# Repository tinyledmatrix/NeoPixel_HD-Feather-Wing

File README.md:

## NeoPixel_HD FeatherWing PCB

More Information and Images also here: https://hackaday.io/project/168448

Inspired and based on Adafruit's NeoPixel FeatherWing, but with more Pixels! This readme is also partly transfered from Adafruit. 

You can find the original here:
http://www.adafruit.com/products/2945  or 
https://github.com/adafruit/Adafruit-NeoPixel-FeatherWing-PCB

This is the NeoPixel FeatherWing, a 9x22 RGB LED Add-on For All Feather Boards! Using Feather Stacking Headers or Feather Female Headers you can connect a FeatherWing on top or bottom of your Feather board and make your Feather board strut like a peacock at a rave.

Put on your sunglasses before staring into these 198 configurable eye-blistering RGB LEDs. Arranged in a 9x22 matrix, each pixel is individually addressable. Only one pin is required to control all the LEDs. On the bottom we have jumpers for the DIN line to any of the I/O pins on a Feather.  Works with any/all of our Feathers! You can cut the default jumper trace and use any pin you like. (In particular, the default pin for Feather Huzzah ESP8266 must be moved, try pin #15!) It works with but is not recommended for ESP32 Feather at this time due to a NeoPixel timing issue that makes it hard to control more than 30 pixels

PCB files for NeoPixel_HD FeatherWing. The format is EagleCAD schematic and board layout

### License

Creative Commons Attribution/Share-Alike, all text above must be included in any redistribution. 
See license.txt for additional information.

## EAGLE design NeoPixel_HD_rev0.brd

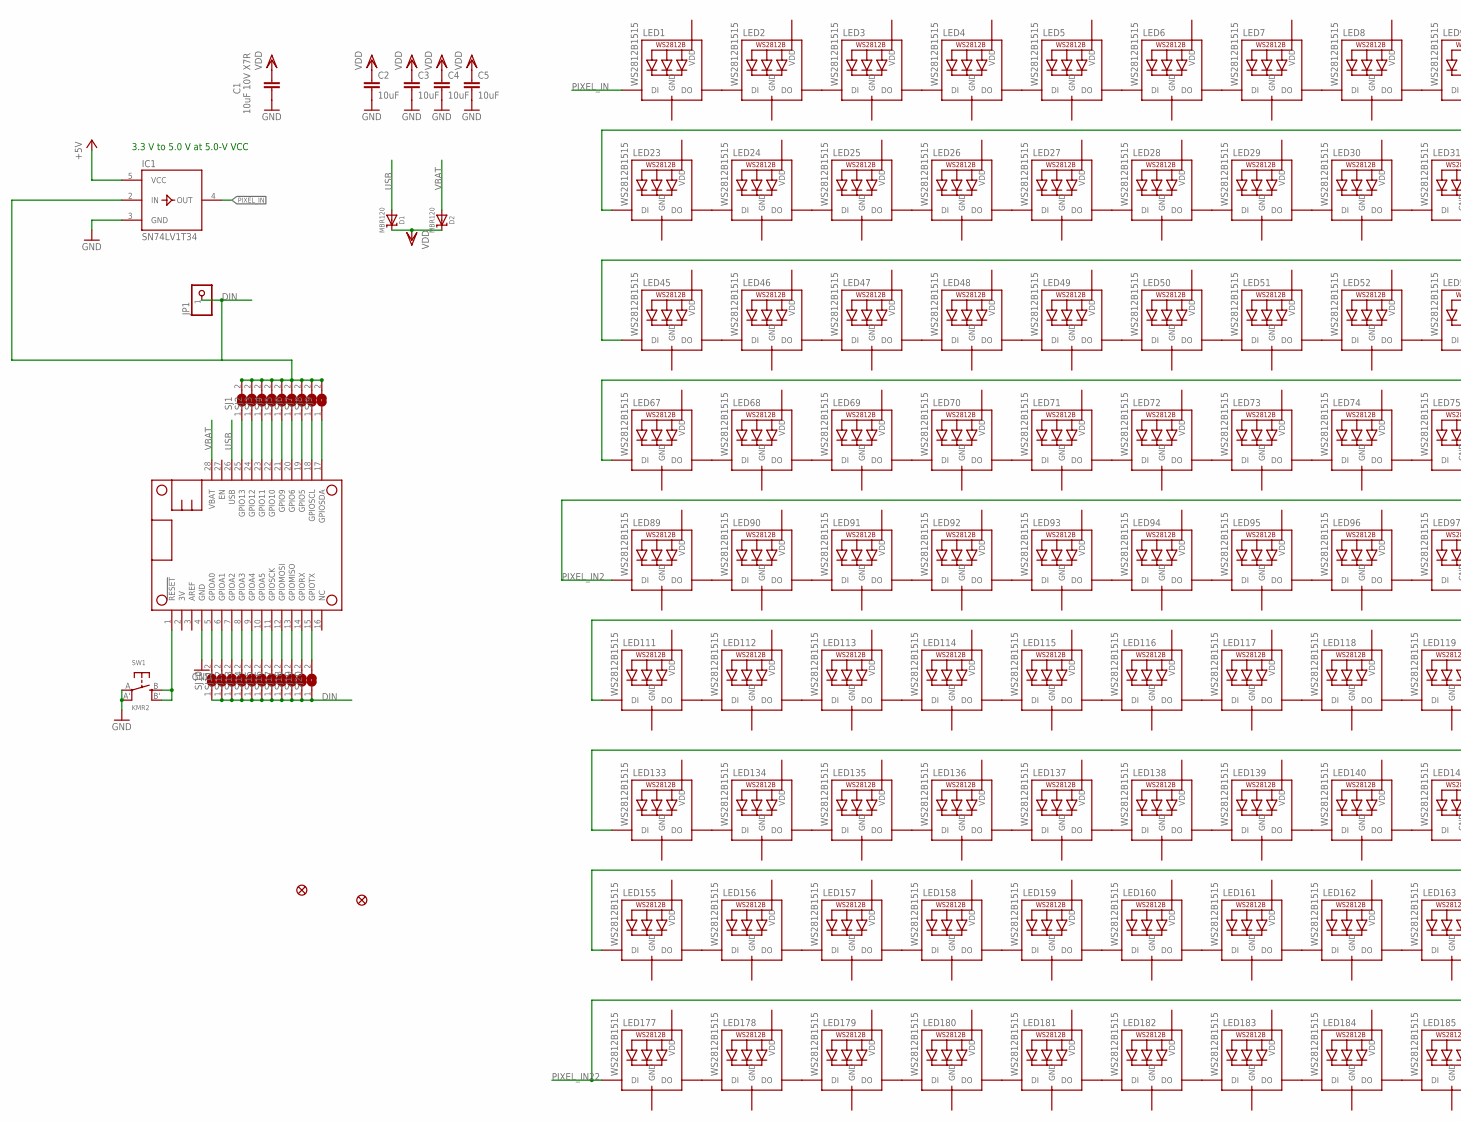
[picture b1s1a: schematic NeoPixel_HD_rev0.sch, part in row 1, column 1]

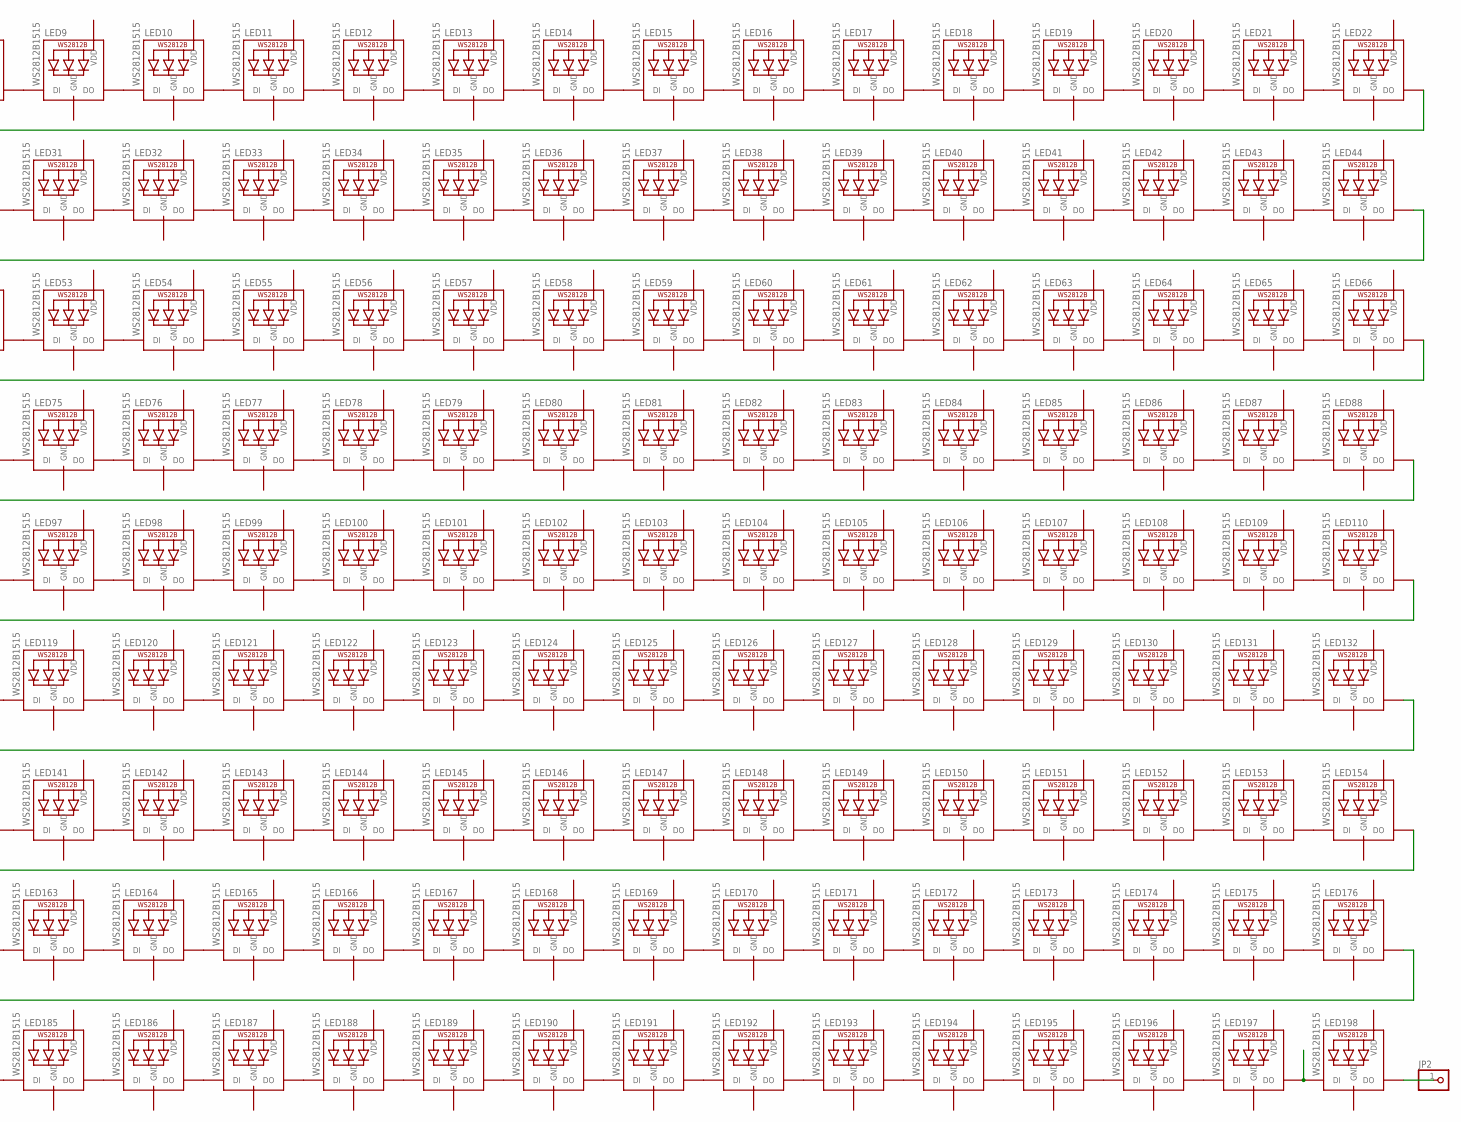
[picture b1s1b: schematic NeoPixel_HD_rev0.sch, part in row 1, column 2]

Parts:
C1: 10uF 10V X7R; C0603-VISHAY
C2, C3, C4, C5: 10uF; C0603-VISHAY
D1, D2: MBR120; SOD-123
FID1, FID2: FIDUCIAL""; FIDUCIAL_1MM
IC1: SN74LV1T34; DCK_R-PDSO-G5
JP1, JP2: HEADER-1X1ROUND; 1X01_ROUND
LED1, LED2, LED3, LED4, LED5, LED6, LED7, LED8, LED9, LED10, LED11, LED12, LED13, LED14, LED15, LED16, LED17, LED18, LED19, LED20, LED21, LED22, LED23, LED24, LED25, LED26, LED27, LED28, LED29, LED30, LED31, LED32, LED33, LED34, LED35, LED36, LED37, LED38, LED39, LED40, LED41, LED42, LED43, LED44, LED45, LED46, LED47, LED48, LED49, LED50, LED51, LED52, LED53, LED54, LED55, LED56, LED57, LED58, LED59, LED60, LED61, LED62, LED63, LED64, LED65, LED66, LED67, LED68, LED69, LED70, LED71, LED72, LED73, LED74, LED75, LED76, LED77, LED78, LED79, LED80, LED81, LED82, LED83, LED84, LED85, LED86, LED87, LED88, LED89, LED90, LED91, LED92, LED93, LED94, LED95, LED96, LED97, LED98, LED99, LED100, LED101, LED102, LED103, LED104, LED105, LED106, LED107, LED108, LED109, LED110, LED111, LED112, LED113, LED114, LED115, LED116, LED117, LED118, LED119, LED120, LED121, LED122, LED123, LED124, LED125, LED126, LED127, LED128, LED129, LED130, LED131, LED132, LED133, LED134, LED135, LED136, LED137, LED138, LED139, LED140, LED141, LED142, LED143, LED144, LED145, LED146, LED147, LED148, LED149, LED150, LED151, LED152, LED153, LED154, LED155, LED156, LED157, LED158, LED159, LED160, LED161, LED162, LED163, LED164, LED165, LED166, LED167, LED168, LED169, LED170, LED171, LED172, LED173, LED174, LED175, LED176, LED177, LED178, LED179, LED180, LED181, LED182, LED183, LED184, LED185, LED186, LED187, LED188, LED189, LED190, LED191, LED192, LED193, LED194, LED195, LED196, LED197, LED198: WS2812B1515; LED1515
MS1: FEATHERWING
SJ1, SJ2, SJ3, SJ4, SJ5, SJ7, SJ8, SJ9, SJ10, SJ11, SJ12, SJ13, SJ14, SJ15, SJ16, SJ17, SJ18, SJ19, SJ20: SOLDERJUMPER; SOLDERJUMPER_ARROW_NOPASTE
SJ6: SOLDERJUMPERCLOSED; SOLDERJUMPER_CLOSEDWIRE
SW1: KMR2; BTN_KMR2_4.6X2.8

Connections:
D6: MS1.20 (GPIO6), SJ6.1
DIN: IC1.2 (IN), JP1.1, SJ1.2, SJ2.2, SJ3.2, SJ4.2, SJ5.2, SJ6.2, SJ7.2, SJ8.2, SJ9.2, SJ10.1, SJ11.1, SJ12.1, SJ13.1, SJ14.1, SJ15.1, SJ16.1, SJ17.1, SJ18.1, SJ19.1, SJ20.1
GND: C1.2, C2.2, C3.2, C4.2, C5.2, IC1.3 (GND), LED1.GND, LED2.GND, LED3.GND, LED4.GND, LED5.GND, LED6.GND, LED7.GND, LED8.GND, LED9.GND, LED10.GND, LED11.GND, LED12.GND, LED13.GND, LED14.GND, LED15.GND, LED16.GND, LED17.GND, LED18.GND, LED19.GND, LED20.GND, LED21.GND, LED22.GND, LED23.GND, LED24.GND, LED25.GND, LED26.GND, LED27.GND, LED28.GND, LED29.GND, LED30.GND, LED31.GND, LED32.GND, LED33.GND, LED34.GND, LED35.GND, LED36.GND, LED37.GND, LED38.GND, LED39.GND, LED40.GND, LED41.GND, LED42.GND, LED43.GND, LED44.GND, LED45.GND, LED46.GND, LED47.GND, LED48.GND, LED49.GND, LED50.GND, LED51.GND, LED52.GND, LED53.GND, LED54.GND, LED55.GND, LED56.GND, LED57.GND, LED58.GND, LED59.GND, LED60.GND, LED61.GND, LED62.GND, LED63.GND, LED64.GND, LED65.GND, LED66.GND, LED67.GND, LED68.GND, LED69.GND, LED70.GND, LED71.GND, LED72.GND, LED73.GND, LED74.GND, LED75.GND, LED76.GND, LED77.GND, LED78.GND, LED79.GND, LED80.GND, LED81.GND, LED82.GND, LED83.GND, LED84.GND, LED85.GND, LED86.GND, LED87.GND, LED88.GND, LED89.GND, LED90.GND, LED91.GND, LED92.GND, LED93.GND, LED94.GND, LED95.GND, LED96.GND, LED97.GND, LED98.GND, LED99.GND, LED100.GND, LED101.GND, LED102.GND, LED103.GND, LED104.GND, LED105.GND, LED106.GND, LED107.GND, LED108.GND, LED109.GND, LED110.GND, LED111.GND, LED112.GND, LED113.GND, LED114.GND, LED115.GND, LED116.GND, LED117.GND, LED118.GND, LED119.GND, LED120.GND, LED121.GND, LED122.GND, LED123.GND, LED124.GND, LED125.GND, LED126.GND, LED127.GND, LED128.GND, LED129.GND, LED130.GND, LED131.GND, LED132.GND, LED133.GND, LED134.GND, LED135.GND, LED136.GND, LED137.GND, LED138.GND, LED139.GND, LED140.GND, LED141.GND, LED142.GND, LED143.GND, LED144.GND, LED145.GND, LED146.GND, LED147.GND, LED148.GND, LED149.GND, LED150.GND, LED151.GND, LED152.GND, LED153.GND, LED154.GND, LED155.GND, LED156.GND, LED157.GND, LED158.GND, LED159.GND, LED160.GND, LED161.GND, LED162.GND, LED163.GND, LED164.GND, LED165.GND, LED166.GND, LED167.GND, LED168.GND, LED169.GND, LED170.GND, LED171.GND, LED172.GND, LED173.GND, LED174.GND, LED175.GND, LED176.GND, LED177.GND, LED178.GND, LED179.GND, LED180.GND, LED181.GND, LED182.GND, LED183.GND, LED184.GND, LED185.GND, LED186.GND, LED187.GND, LED188.GND, LED189.GND, LED190.GND, LED191.GND, LED192.GND, LED193.GND, LED194.GND, LED195.GND, LED196.GND, LED197.GND, LED198.GND, MS1.4 (GND), SW1.A, SW1.A' (P1)
unnamed: LED42.DOUT (DO), LED43.DIN (DI)
unnamed: LED43.DOUT (DO), LED44.DIN (DI)
unnamed: MS1.25 (GPIO13), SJ1.1
unnamed: MS1.15 (GPIOTX), SJ20.2
unnamed: MS1.24 (GPIO12), SJ2.1
unnamed: MS1.14 (GPIORX), SJ19.2
unnamed: MS1.13 (GPIOMISO), SJ18.2
unnamed: MS1.12 (GPIOMOSI), SJ17.2
unnamed: MS1.11 (GPIOSCK), SJ16.2
unnamed: MS1.10 (GPIOA5), SJ15.2
unnamed: MS1.9 (GPIOA4), SJ14.2
unnamed: MS1.8 (GPIOA3), SJ13.2
unnamed: MS1.7 (GPIOA2), SJ12.2
unnamed: MS1.6 (GPIOA1), SJ11.2
unnamed: MS1.5 (GPIOA0), SJ10.2
unnamed: LED14.DOUT (DO), LED15.DIN (DI)
unnamed: LED45.DOUT (DO), LED46.DIN (DI)
unnamed: MS1.1 (!RESET), SW1.B (S), SW1.B' (S1)
unnamed: MS1.23 (GPIO11), SJ3.1
unnamed: MS1.22 (GPIO10), SJ4.1
unnamed: MS1.21 (GPIO9), SJ5.1
unnamed: JP2.1, LED198.DOUT (DO)
unnamed: MS1.19 (GPIO5), SJ7.1
unnamed: MS1.18 (GPIOSCL), SJ8.1
unnamed: MS1.17 (GPIOSDA), SJ9.1
unnamed: LED46.DOUT (DO), LED47.DIN (DI)
unnamed: LED47.DOUT (DO), LED48.DIN (DI)
unnamed: LED48.DOUT (DO), LED49.DIN (DI)
unnamed: LED49.DOUT (DO), LED50.DIN (DI)
unnamed: LED50.DOUT (DO), LED51.DIN (DI)
unnamed: LED51.DOUT (DO), LED52.DIN (DI)
unnamed: LED52.DOUT (DO), LED53.DIN (DI)
unnamed: LED54.DOUT (DO), LED55.DIN (DI)
unnamed: LED53.DOUT (DO), LED54.DIN (DI)
unnamed: LED55.DOUT (DO), LED56.DIN (DI)
unnamed: LED56.DOUT (DO), LED57.DIN (DI)
unnamed: LED59.DOUT (DO), LED60.DIN (DI)
unnamed: LED60.DOUT (DO), LED61.DIN (DI)
unnamed: LED61.DOUT (DO), LED62.DIN (DI)
unnamed: LED62.DOUT (DO), LED63.DIN (DI)
unnamed: LED63.DOUT (DO), LED64.DIN (DI)
unnamed: LED64.DOUT (DO), LED65.DIN (DI)
unnamed: LED65.DOUT (DO), LED66.DIN (DI)
unnamed: LED66.DOUT (DO), LED67.DIN (DI)
unnamed: LED68.DOUT (DO), LED69.DIN (DI)
unnamed: LED67.DOUT (DO), LED68.DIN (DI)
unnamed: LED69.DOUT (DO), LED70.DIN (DI)
unnamed: LED70.DOUT (DO), LED71.DIN (DI)
unnamed: LED73.DOUT (DO), LED74.DIN (DI)
unnamed: LED74.DOUT (DO), LED75.DIN (DI)
unnamed: LED75.DOUT (DO), LED76.DIN (DI)
unnamed: LED76.DOUT (DO), LED77.DIN (DI)
unnamed: LED77.DOUT (DO), LED78.DIN (DI)
unnamed: LED1.DOUT (DO), LED2.DIN (DI)
unnamed: LED2.DOUT (DO), LED3.DIN (DI)
unnamed: LED3.DOUT (DO), LED4.DIN (DI)
unnamed: LED4.DOUT (DO), LED5.DIN (DI)
unnamed: LED5.DOUT (DO), LED6.DIN (DI)
unnamed: LED6.DOUT (DO), LED7.DIN (DI)
unnamed: LED7.DOUT (DO), LED8.DIN (DI)
unnamed: LED8.DOUT (DO), LED9.DIN (DI)
unnamed: LED10.DOUT (DO), LED11.DIN (DI)
unnamed: LED9.DOUT (DO), LED10.DIN (DI)
unnamed: LED11.DOUT (DO), LED12.DIN (DI)
unnamed: LED12.DOUT (DO), LED13.DIN (DI)
unnamed: LED15.DOUT (DO), LED16.DIN (DI)
unnamed: LED16.DOUT (DO), LED17.DIN (DI)
unnamed: LED17.DOUT (DO), LED18.DIN (DI)
unnamed: LED18.DOUT (DO), LED19.DIN (DI)
unnamed: LED19.DOUT (DO), LED20.DIN (DI)
unnamed: LED20.DOUT (DO), LED21.DIN (DI)
unnamed: LED21.DOUT (DO), LED22.DIN (DI)
unnamed: LED22.DOUT (DO), LED23.DIN (DI)
unnamed: LED24.DOUT (DO), LED25.DIN (DI)
unnamed: LED23.DOUT (DO), LED24.DIN (DI)
unnamed: LED25.DOUT (DO), LED26.DIN (DI)
unnamed: LED26.DOUT (DO), LED27.DIN (DI)
unnamed: LED29.DOUT (DO), LED30.DIN (DI)
unnamed: LED30.DOUT (DO), LED31.DIN (DI)
unnamed: LED31.DOUT (DO), LED32.DIN (DI)
unnamed: LED32.DOUT (DO), LED33.DIN (DI)
unnamed: LED33.DOUT (DO), LED34.DIN (DI)
unnamed: LED34.DOUT (DO), LED35.DIN (DI)
unnamed: LED35.DOUT (DO), LED36.DIN (DI)
unnamed: LED36.DOUT (DO), LED37.DIN (DI)
unnamed: LED38.DOUT (DO), LED39.DIN (DI)
unnamed: LED37.DOUT (DO), LED38.DIN (DI)
unnamed: LED39.DOUT (DO), LED40.DIN (DI)
unnamed: LED40.DOUT (DO), LED41.DIN (DI)
unnamed: LED13.DOUT (DO), LED14.DIN (DI)
unnamed: LED27.DOUT (DO), LED28.DIN (DI)
unnamed: LED41.DOUT (DO), LED42.DIN (DI)
unnamed: LED78.DOUT (DO), LED79.DIN (DI)
unnamed: LED28.DOUT (DO), LED29.DIN (DI)
unnamed: LED79.DOUT (DO), LED80.DIN (DI)
unnamed: LED80.DOUT (DO), LED81.DIN (DI)
unnamed: LED82.DOUT (DO), LED83.DIN (DI)
unnamed: LED81.DOUT (DO), LED82.DIN (DI)
unnamed: LED83.DOUT (DO), LED84.DIN (DI)
unnamed: LED84.DOUT (DO), LED85.DIN (DI)
unnamed: LED57.DOUT (DO), LED58.DIN (DI)
unnamed: LED71.DOUT (DO), LED72.DIN (DI)
unnamed: LED85.DOUT (DO), LED86.DIN (DI)
unnamed: LED72.DOUT (DO), LED73.DIN (DI)
unnamed: LED86.DOUT (DO), LED87.DIN (DI)
unnamed: LED87.DOUT (DO), LED88.DIN (DI)
unnamed: LED58.DOUT (DO), LED59.DIN (DI)
unnamed: LED89.DOUT (DO), LED90.DIN (DI)
unnamed: LED90.DOUT (DO), LED91.DIN (DI)
unnamed: LED91.DOUT (DO), LED92.DIN (DI)
unnamed: LED92.DOUT (DO), LED93.DIN (DI)
unnamed: LED93.DOUT (DO), LED94.DIN (DI)
unnamed: LED94.DOUT (DO), LED95.DIN (DI)
unnamed: LED95.DOUT (DO), LED96.DIN (DI)
unnamed: LED96.DOUT (DO), LED97.DIN (DI)
unnamed: LED98.DOUT (DO), LED99.DIN (DI)
unnamed: LED97.DOUT (DO), LED98.DIN (DI)
unnamed: LED99.DOUT (DO), LED100.DIN (DI)
unnamed: LED100.DOUT (DO), LED101.DIN (DI)
unnamed: LED103.DOUT (DO), LED104.DIN (DI)
unnamed: LED104.DOUT (DO), LED105.DIN (DI)
unnamed: LED105.DOUT (DO), LED106.DIN (DI)
unnamed: LED106.DOUT (DO), LED107.DIN (DI)
unnamed: LED107.DOUT (DO), LED108.DIN (DI)
unnamed: LED108.DOUT (DO), LED109.DIN (DI)
unnamed: LED109.DOUT (DO), LED110.DIN (DI)
unnamed: LED110.DOUT (DO), LED111.DIN (DI)
unnamed: LED112.DOUT (DO), LED113.DIN (DI)
unnamed: LED111.DOUT (DO), LED112.DIN (DI)
unnamed: LED113.DOUT (DO), LED114.DIN (DI)
unnamed: LED114.DOUT (DO), LED115.DIN (DI)
unnamed: LED117.DOUT (DO), LED118.DIN (DI)
unnamed: LED118.DOUT (DO), LED119.DIN (DI)
unnamed: LED119.DOUT (DO), LED120.DIN (DI)
unnamed: LED120.DOUT (DO), LED121.DIN (DI)
unnamed: LED121.DOUT (DO), LED122.DIN (DI)
unnamed: LED122.DOUT (DO), LED123.DIN (DI)
unnamed: LED123.DOUT (DO), LED124.DIN (DI)
unnamed: LED124.DOUT (DO), LED125.DIN (DI)
unnamed: LED126.DOUT (DO), LED127.DIN (DI)
unnamed: LED125.DOUT (DO), LED126.DIN (DI)
unnamed: LED127.DOUT (DO), LED128.DIN (DI)
unnamed: LED128.DOUT (DO), LED129.DIN (DI)
unnamed: LED101.DOUT (DO), LED102.DIN (DI)
unnamed: LED115.DOUT (DO), LED116.DIN (DI)
unnamed: LED129.DOUT (DO), LED130.DIN (DI)
unnamed: LED116.DOUT (DO), LED117.DIN (DI)
unnamed: LED130.DOUT (DO), LED131.DIN (DI)
unnamed: LED131.DOUT (DO), LED132.DIN (DI)
unnamed: LED102.DOUT (DO), LED103.DIN (DI)
unnamed: LED133.DOUT (DO), LED134.DIN (DI)
unnamed: LED134.DOUT (DO), LED135.DIN (DI)
unnamed: LED135.DOUT (DO), LED136.DIN (DI)
unnamed: LED136.DOUT (DO), LED137.DIN (DI)
unnamed: LED137.DOUT (DO), LED138.DIN (DI)
unnamed: LED138.DOUT (DO), LED139.DIN (DI)
unnamed: LED139.DOUT (DO), LED140.DIN (DI)
unnamed: LED140.DOUT (DO), LED141.DIN (DI)
unnamed: LED142.DOUT (DO), LED143.DIN (DI)
unnamed: LED141.DOUT (DO), LED142.DIN (DI)
unnamed: LED143.DOUT (DO), LED144.DIN (DI)
unnamed: LED144.DOUT (DO), LED145.DIN (DI)
unnamed: LED147.DOUT (DO), LED148.DIN (DI)
unnamed: LED148.DOUT (DO), LED149.DIN (DI)
unnamed: LED149.DOUT (DO), LED150.DIN (DI)
unnamed: LED150.DOUT (DO), LED151.DIN (DI)
unnamed: LED151.DOUT (DO), LED152.DIN (DI)
unnamed: LED152.DOUT (DO), LED153.DIN (DI)
unnamed: LED153.DOUT (DO), LED154.DIN (DI)
unnamed: LED154.DOUT (DO), LED155.DIN (DI)
unnamed: LED156.DOUT (DO), LED157.DIN (DI)
unnamed: LED155.DOUT (DO), LED156.DIN (DI)
unnamed: LED157.DOUT (DO), LED158.DIN (DI)
unnamed: LED158.DOUT (DO), LED159.DIN (DI)
unnamed: LED161.DOUT (DO), LED162.DIN (DI)
unnamed: LED162.DOUT (DO), LED163.DIN (DI)
unnamed: LED163.DOUT (DO), LED164.DIN (DI)
unnamed: LED164.DOUT (DO), LED165.DIN (DI)
unnamed: LED165.DOUT (DO), LED166.DIN (DI)
unnamed: LED166.DOUT (DO), LED167.DIN (DI)
unnamed: LED167.DOUT (DO), LED168.DIN (DI)
unnamed: LED168.DOUT (DO), LED169.DIN (DI)
unnamed: LED170.DOUT (DO), LED171.DIN (DI)
unnamed: LED169.DOUT (DO), LED170.DIN (DI)
unnamed: LED171.DOUT (DO), LED172.DIN (DI)
unnamed: LED172.DOUT (DO), LED173.DIN (DI)
unnamed: LED145.DOUT (DO), LED146.DIN (DI)
unnamed: LED159.DOUT (DO), LED160.DIN (DI)
unnamed: LED173.DOUT (DO), LED174.DIN (DI)
unnamed: LED160.DOUT (DO), LED161.DIN (DI)
unnamed: LED174.DOUT (DO), LED175.DIN (DI)
unnamed: LED175.DOUT (DO), LED176.DIN (DI)
unnamed: LED146.DOUT (DO), LED147.DIN (DI)
unnamed: LED177.DOUT (DO), LED178.DIN (DI)
unnamed: LED178.DOUT (DO), LED179.DIN (DI)
unnamed: LED179.DOUT (DO), LED180.DIN (DI)
unnamed: LED180.DOUT (DO), LED181.DIN (DI)
unnamed: LED181.DOUT (DO), LED182.DIN (DI)
unnamed: LED182.DOUT (DO), LED183.DIN (DI)
unnamed: LED183.DOUT (DO), LED184.DIN (DI)
unnamed: LED184.DOUT (DO), LED185.DIN (DI)
unnamed: LED186.DOUT (DO), LED187.DIN (DI)
unnamed: LED185.DOUT (DO), LED186.DIN (DI)
unnamed: LED187.DOUT (DO), LED188.DIN (DI)
unnamed: LED188.DOUT (DO), LED189.DIN (DI)
unnamed: LED191.DOUT (DO), LED192.DIN (DI)
unnamed: LED192.DOUT (DO), LED193.DIN (DI)
unnamed: LED193.DOUT (DO), LED194.DIN (DI)
unnamed: LED194.DOUT (DO), LED195.DIN (DI)
unnamed: LED195.DOUT (DO), LED196.DIN (DI)
unnamed: LED196.DOUT (DO), LED197.DIN (DI)
unnamed: LED197.DOUT (DO), LED198.DIN (DI)
unnamed: LED190.DOUT (DO), LED191.DIN (DI)
unnamed: LED189.DOUT (DO), LED190.DIN (DI)
PIXEL_IN: IC1.4 (OUT), LED1.DIN (DI)
PIXEL_IN1: LED44.DOUT (DO), LED45.DIN (DI)
PIXEL_IN2: LED88.DOUT (DO), LED89.DIN (DI)
PIXEL_IN11: LED132.DOUT (DO), LED133.DIN (DI)
PIXEL_IN22: LED176.DOUT (DO), LED177.DIN (DI)
USB: D1.A, MS1.26 (USB)
VBAT: D2.A, MS1.28 (VBAT)
VDD: C1.1, C2.1, C3.1, C4.1, C5.1, D1.C, D2.C, IC1.5 (VCC), LED1.VDD, LED2.VDD, LED3.VDD, LED4.VDD, LED5.VDD, LED6.VDD, LED7.VDD, LED8.VDD, LED9.VDD, LED10.VDD, LED11.VDD, LED12.VDD, LED13.VDD, LED14.VDD, LED15.VDD, LED16.VDD, LED17.VDD, LED18.VDD, LED19.VDD, LED20.VDD, LED21.VDD, LED22.VDD, LED23.VDD, LED24.VDD, LED25.VDD, LED26.VDD, LED27.VDD, LED28.VDD, LED29.VDD, LED30.VDD, LED31.VDD, LED32.VDD, LED33.VDD, LED34.VDD, LED35.VDD, LED36.VDD, LED37.VDD, LED38.VDD, LED39.VDD, LED40.VDD, LED41.VDD, LED42.VDD, LED43.VDD, LED44.VDD, LED45.VDD, LED46.VDD, LED47.VDD, LED48.VDD, LED49.VDD, LED50.VDD, LED51.VDD, LED52.VDD, LED53.VDD, LED54.VDD, LED55.VDD, LED56.VDD, LED57.VDD, LED58.VDD, LED59.VDD, LED60.VDD, LED61.VDD, LED62.VDD, LED63.VDD, LED64.VDD, LED65.VDD, LED66.VDD, LED67.VDD, LED68.VDD, LED69.VDD, LED70.VDD, LED71.VDD, LED72.VDD, LED73.VDD, LED74.VDD, LED75.VDD, LED76.VDD, LED77.VDD, LED78.VDD, LED79.VDD, LED80.VDD, LED81.VDD, LED82.VDD, LED83.VDD, LED84.VDD, LED85.VDD, LED86.VDD, LED87.VDD, LED88.VDD, LED89.VDD, LED90.VDD, LED91.VDD, LED92.VDD, LED93.VDD, LED94.VDD, LED95.VDD, LED96.VDD, LED97.VDD, LED98.VDD, LED99.VDD, LED100.VDD, LED101.VDD, LED102.VDD, LED103.VDD, LED104.VDD, LED105.VDD, LED106.VDD, LED107.VDD, LED108.VDD, LED109.VDD, LED110.VDD, LED111.VDD, LED112.VDD, LED113.VDD, LED114.VDD, LED115.VDD, LED116.VDD, LED117.VDD, LED118.VDD, LED119.VDD, LED120.VDD, LED121.VDD, LED122.VDD, LED123.VDD, LED124.VDD, LED125.VDD, LED126.VDD, LED127.VDD, LED128.VDD, LED129.VDD, LED130.VDD, LED131.VDD, LED132.VDD, LED133.VDD, LED134.VDD, LED135.VDD, LED136.VDD, LED137.VDD, LED138.VDD, LED139.VDD, LED140.VDD, LED141.VDD, LED142.VDD, LED143.VDD, LED144.VDD, LED145.VDD, LED146.VDD, LED147.VDD, LED148.VDD, LED149.VDD, LED150.VDD, LED151.VDD, LED152.VDD, LED153.VDD, LED154.VDD, LED155.VDD, LED156.VDD, LED157.VDD, LED158.VDD, LED159.VDD, LED160.VDD, LED161.VDD, LED162.VDD, LED163.VDD, LED164.VDD, LED165.VDD, LED166.VDD, LED167.VDD, LED168.VDD, LED169.VDD, LED170.VDD, LED171.VDD, LED172.VDD, LED173.VDD, LED174.VDD, LED175.VDD, LED176.VDD, LED177.VDD, LED178.VDD, LED179.VDD, LED180.VDD, LED181.VDD, LED182.VDD, LED183.VDD, LED184.VDD, LED185.VDD, LED186.VDD, LED187.VDD, LED188.VDD, LED189.VDD, LED190.VDD, LED191.VDD, LED192.VDD, LED193.VDD, LED194.VDD, LED195.VDD, LED196.VDD, LED197.VDD, LED198.VDD

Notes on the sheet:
3.3 V to 5.0 V at 5.0-V VCC

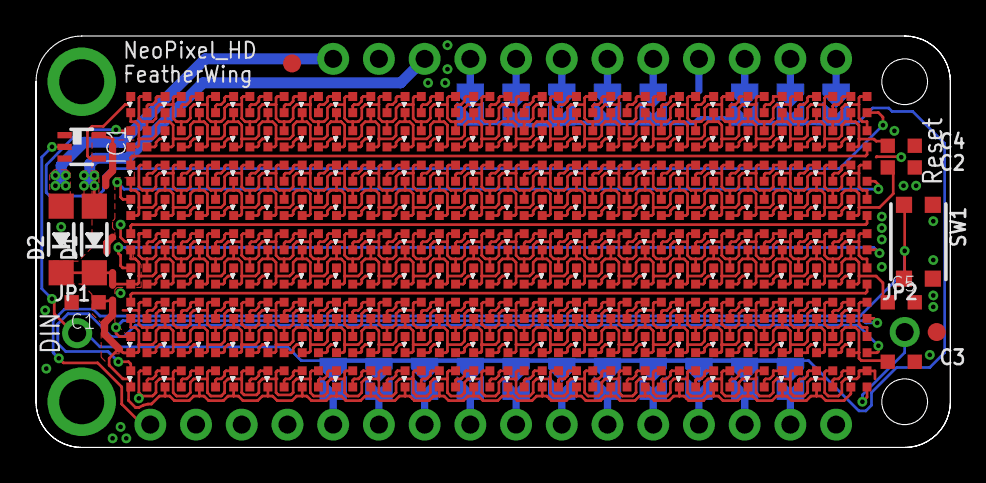
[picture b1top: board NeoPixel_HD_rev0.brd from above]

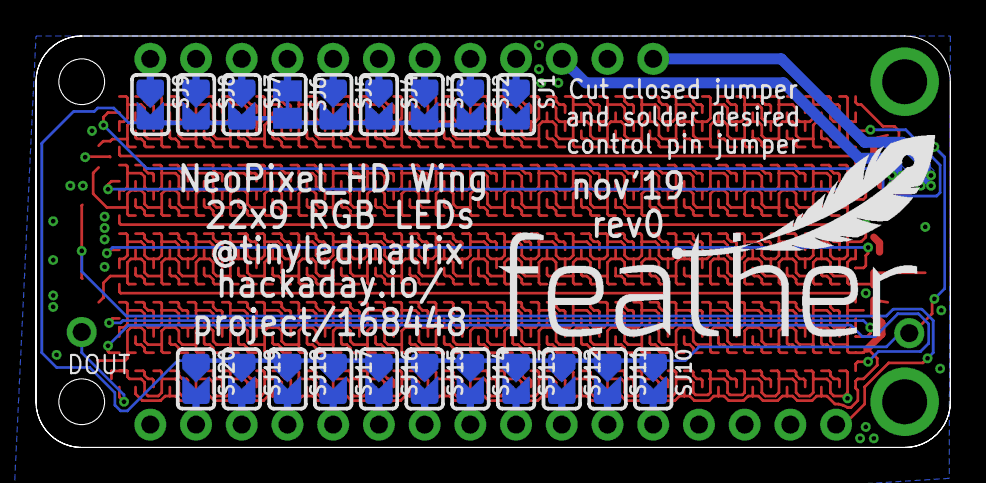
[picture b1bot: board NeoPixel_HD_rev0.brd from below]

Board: 2 copper layers, 50.8 x 22.9 mm, 233 parts (21 on the bottom side), 225 nets.

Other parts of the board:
U$3: FEATHERLOGO

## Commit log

2021-01-23 Push data to Github
    push all the data to github
